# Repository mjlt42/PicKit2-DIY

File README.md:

PicKit 2 Bootloader Clone

# Description
This is clone of a PicKit 2, which is a bootloader for PIC MCU chips; requires a pre programmed chip to opperate. 

## Schematic:

## Bill Of Materials
| Reference | Qty | Value | Footprint | Datasheet |
| :--- | :---: | :--- | :--- | :--- |
| C1 | 1 | 47uF | JLCImport:ERS1KM470F12OT | — |
| C2, C3 | 2 | 22pF | JLCImport:CC1H220KA1EDCH4B1100 | — |
| C4 | 1 | 0.47uF | JLCImport:178MU0009 | — |
| C5 | 1 | 0.1uF | JLCImport:178MU0006 | — |
| D1 | 1 | BAT41 | JLCImport:BAT41 | [Datasheet](http://www.vishay.com/docs/85659/bat41.pdf) |
| D2 | 1 | 1N5817 | JLCImport:1N5817_C7544876 | [Datasheet](http://www.vishay.com/docs/88525/1n5817.pdf) |
| D3, D4 | 2 | LED | LED_THT:LED_D5.0mm | — |
| J1 | 1 | Conn_01x06_Socket | JLCImport:2_54-1_6PHeader-RA | — |
| J4 | 1 | USB_C_Receptacle_USB2.0_16P | JLCImport:KH-TYPE-C-16P | [Link](https://www.usb.org/sites/default/files/documents/usb_type-c.zip) |
| L1 | 1 | 680uH | JLCImport:YAL0410-681K | — |
| Q1, Q2, Q4 | 3 | 2N3904 | JLCImport:2N3904_C2874602 | [Datasheet](https://www.onsemi.com/pub/Collateral/2N3903-D.PDF) |
| Q3 | 1 | 2N3906 | JLCImport:2N3906_C2874603 | [Datasheet](https://www.onsemi.com/pub/Collateral/2N3906-D.PDF) |
| R1 | 1 | 1K | JLCImport:MF1_4W-1K_1_T52 | — |
| R2, R10, R15, R16 | 4 | 4.7K | JLCImport:MF1_4W-4_7K_1_T52 | — |
| R3 | 1 | 2.7K | JLCImport:MF1_4W-2_7K_1_T52 | — |
| R4 | 1 | 100K | JLCImport:MF1_4W-100K_1_T52 | — |
| R5, R6, R9 | 3 | 10K | JLCImport:MFR0W4F1002A50 | — |
| R7, R11 | 2 | 330 | JLCImport:MFR0W4F3300A50 | — |
| R8, R12, R13, R17 | 4 | 100 | JLCImport:MFR0W4F1000A50 | — |
| R14 | 1 | 22K | JLCImport:MF1_4W-22K_1_T52 | — |
| R18, R19 | 2 | 5.1K | JLCImport:MF1_4W-5_1K_1_T52 | — |
| SW1 | 1 | SW_Push | Button_Switch_THT:SW_PUSH_6mm | — |
| U1 | 1 | PIC18F2550-ISP | Package_DIP:DIP-28_W7.62mm | [Datasheet](http://ww1.microchip.com/downloads/en/devicedoc/39632c.pdf) |
| X1 | 1 | 20Mhz | JLCImport:X49ST2-20_000-F20JGDT | — |

## PCB Layout:

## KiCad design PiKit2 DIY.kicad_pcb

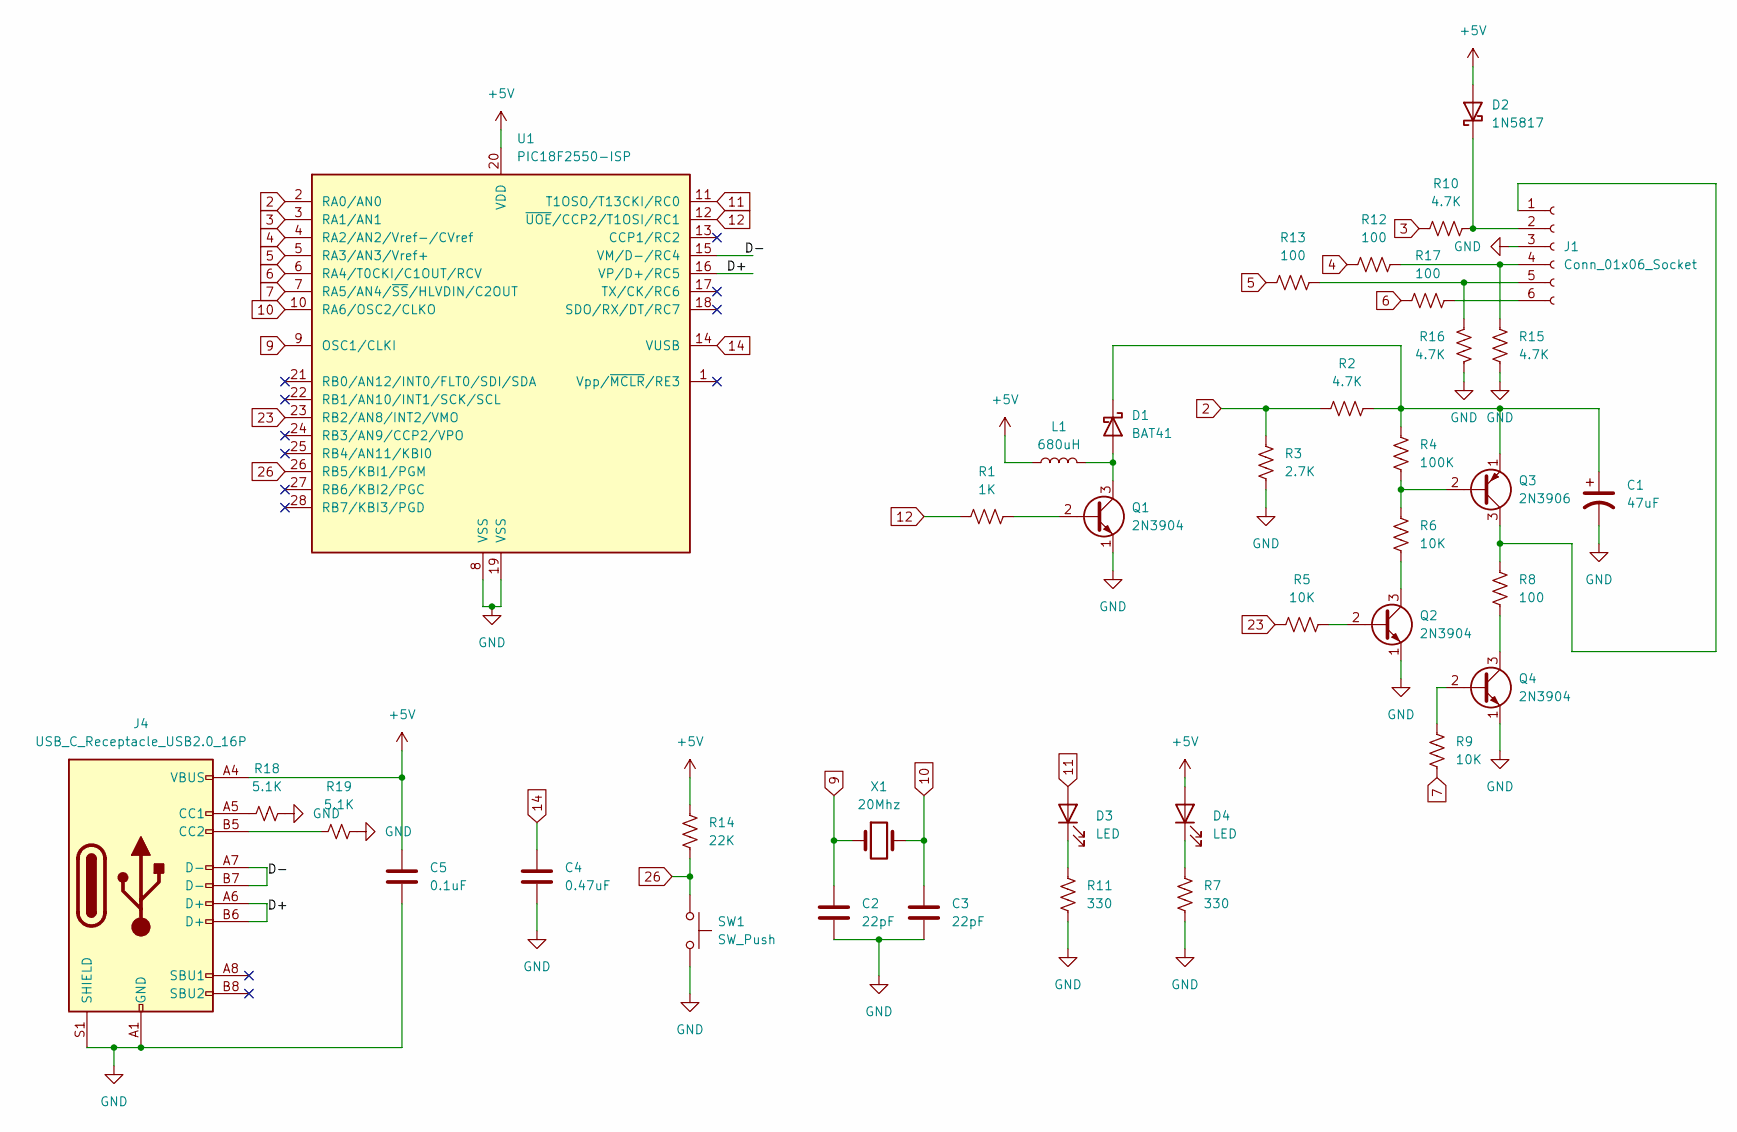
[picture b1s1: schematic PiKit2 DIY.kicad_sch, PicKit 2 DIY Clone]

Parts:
C1: 47uF; ERS1KM470F12OT
C2, C3: 22pF; CC1H220KA1EDCH4B1100
C4: 0.47uF; 178MU0009
C5: 0.1uF; 178MU0006
D1: BAT41
D2: 1N5817; 1N5817_C7544876
D3, D4: LED; LED_D5.0mm
J1: Conn_01x06_Socket; 2_54-1_6PHeader-RA
J4: USB_C_Receptacle_USB2.0_16P; KH-TYPE-C-16P
L1: 680uH; YAL0410-681K
Q1, Q2, Q4: 2N3904; 2N3904_C2874602
Q3: 2N3906; 2N3906_C2874603
R1: 1K; MF1_4W-1K_1_T52
R2, R10, R15, R16: 4.7K; MF1_4W-4_7K_1_T52
R3: 2.7K; MF1_4W-2_7K_1_T52
R4: 100K; MF1_4W-100K_1_T52
R5, R6, R9: 10K; MFR0W4F1002A50
R7, R11: 330; MFR0W4F3300A50
R8, R12, R13, R17: 100; MFR0W4F1000A50
R14: 22K; MF1_4W-22K_1_T52
R18, R19: 5.1K; MF1_4W-5_1K_1_T52
SW1: SW_Push; SW_PUSH_6mm
U1: PIC18F2550-ISP; DIP-28_W7.62mm
X1: 20Mhz; X49ST2-20_000-F20JGDT

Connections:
2: R2.1, R3.1, U1.2 (RA0/AN0)
3: R10.1, U1.3 (RA1/AN1)
4: R12.1, U1.4 (RA2/AN2/Vref-/CVref)
5: R13.1, U1.5 (RA3/AN3/Vref+)
6: R17.1, U1.6 (RA4/T0CKI/C1OUT/RCV)
7: R9.2, U1.7 (RA5/AN4/~SS/HLVDIN/C2OUT)
9: C2.1, U1.9 (OSC1/CLKI), X1.1
10: C3.1, U1.10 (RA6/OSC2/CLKO), X1.2
11: D3.2 (A), U1.11 (T1OSO/T13CKI/RC0)
12: R1.1, U1.12 (~UOE/CCP2/T1OSI/RC1)
14: C4.1, U1.14 (VUSB)
23: R5.1, U1.23 (RB2/AN8/INT2/VMO)
26: R14.2, SW1.1, U1.26 (RB5/KBI1/PGM)
+5V: C5.1, D2.2 (A), D4.2 (A), J4.A4 (VBUS), J4.A9 (VBUS), J4.B4 (VBUS), J4.B9 (VBUS), L1.1, R14.1, U1.20 (VDD)
/D+: J4.A6 (D+), J4.B6 (D+), U1.16 (VP/D+/RC5)
/D-: J4.A7 (D-), J4.B7 (D-), U1.15 (VM/D-/RC4)
GND: C1.2, C2.2, C3.2, C4.2, C5.2, J1.3, J4.A1 (GND), J4.A12 (GND), J4.B1 (GND), J4.B12 (GND), J4.S1 (SHIELD), Q1.1 (E), Q2.1 (E), Q4.1 (E), R3.2, R7.2, R11.2, R15.1, R16.2, R18.2, R19.2, SW1.2, U1.8 (VSS), U1.19 (VSS)
unnamed: D1.2 (A), L1.2, Q1.3 (C)
unnamed: C1.1, D1.1 (K), Q3.1 (E), R2.2, R4.1
unnamed: D2.1 (K), J1.2, R10.2
unnamed: D3.1 (K), R11.1
unnamed: D4.1 (K), R7.1
unnamed: J1.1, Q3.3 (C), R8.1
unnamed: J1.4, R12.2, R15.2
unnamed: J1.5, R13.2, R16.1
unnamed: J1.6, R17.2
unnamed: J4.A5 (CC1), R18.1
unnamed: J4.B5 (CC2), R19.1
unnamed: Q1.2 (B), R1.2
unnamed: Q2.2 (B), R5.2
unnamed: Q2.3 (C), R6.2
unnamed: Q3.2 (B), R4.2, R6.1
unnamed: Q4.2 (B), R9.1
unnamed: Q4.3 (C), R8.2

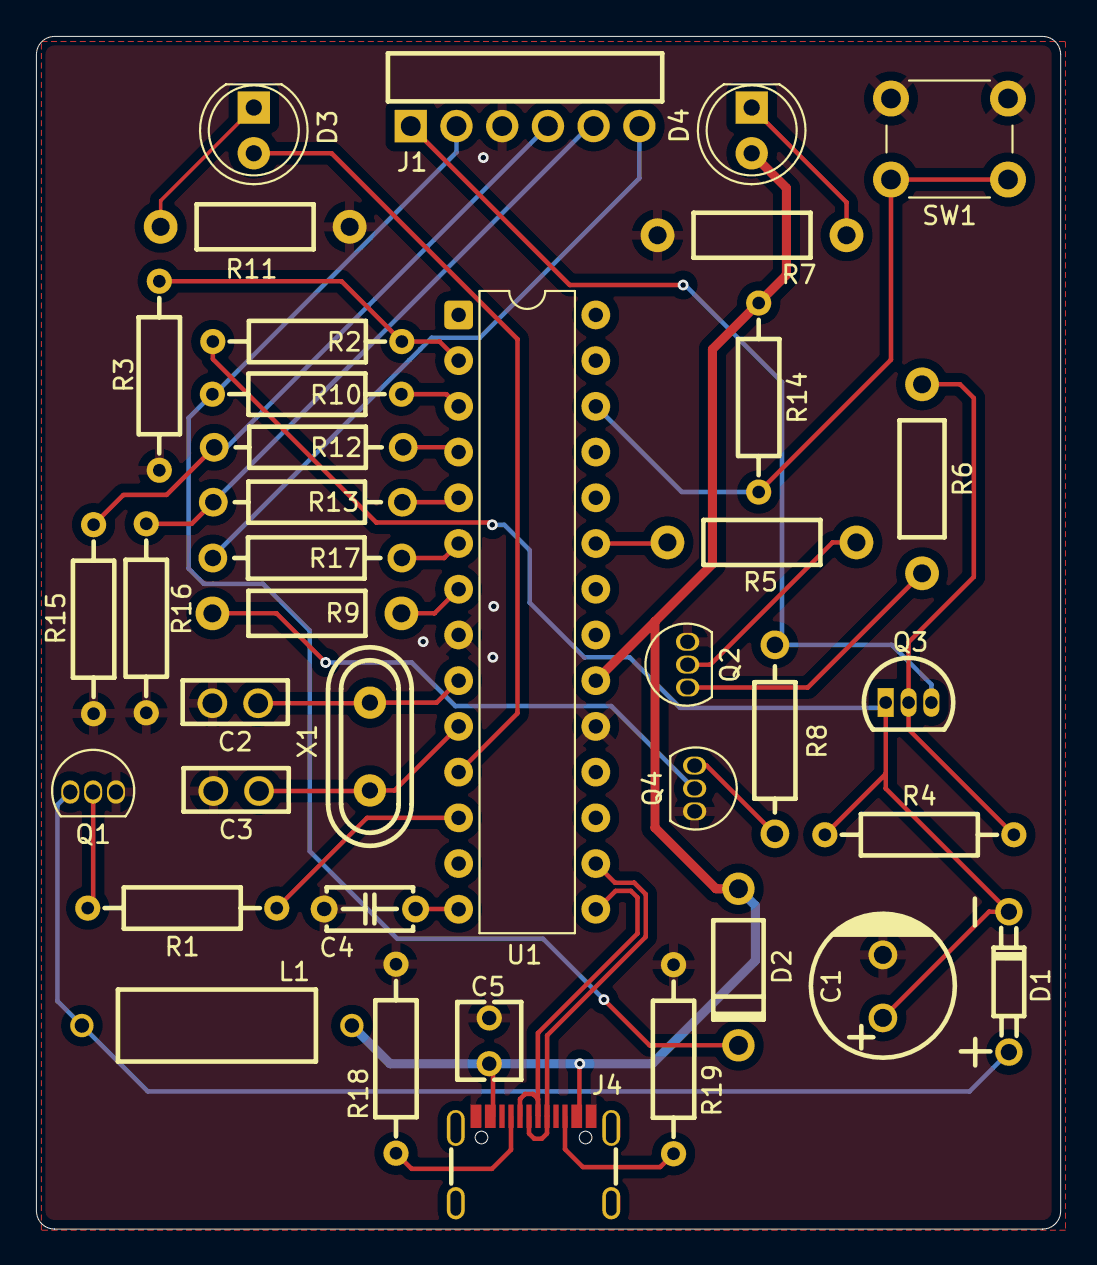
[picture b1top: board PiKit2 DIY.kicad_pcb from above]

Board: 2 copper layers, 56.9 x 66.3 mm, 38 parts (0 on the bottom side), 34 nets.
